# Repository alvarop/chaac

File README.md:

# Chaac - Weather station!

This is a work in progress for a wireless weather station project.

The project consists of:

* [Hardware](hw/) - Main development board design files
* [Firmware](fw/) - Code for the microcontroller
* [Software](sw/) - Python scripts to communicate with the weather station, log, and plot data

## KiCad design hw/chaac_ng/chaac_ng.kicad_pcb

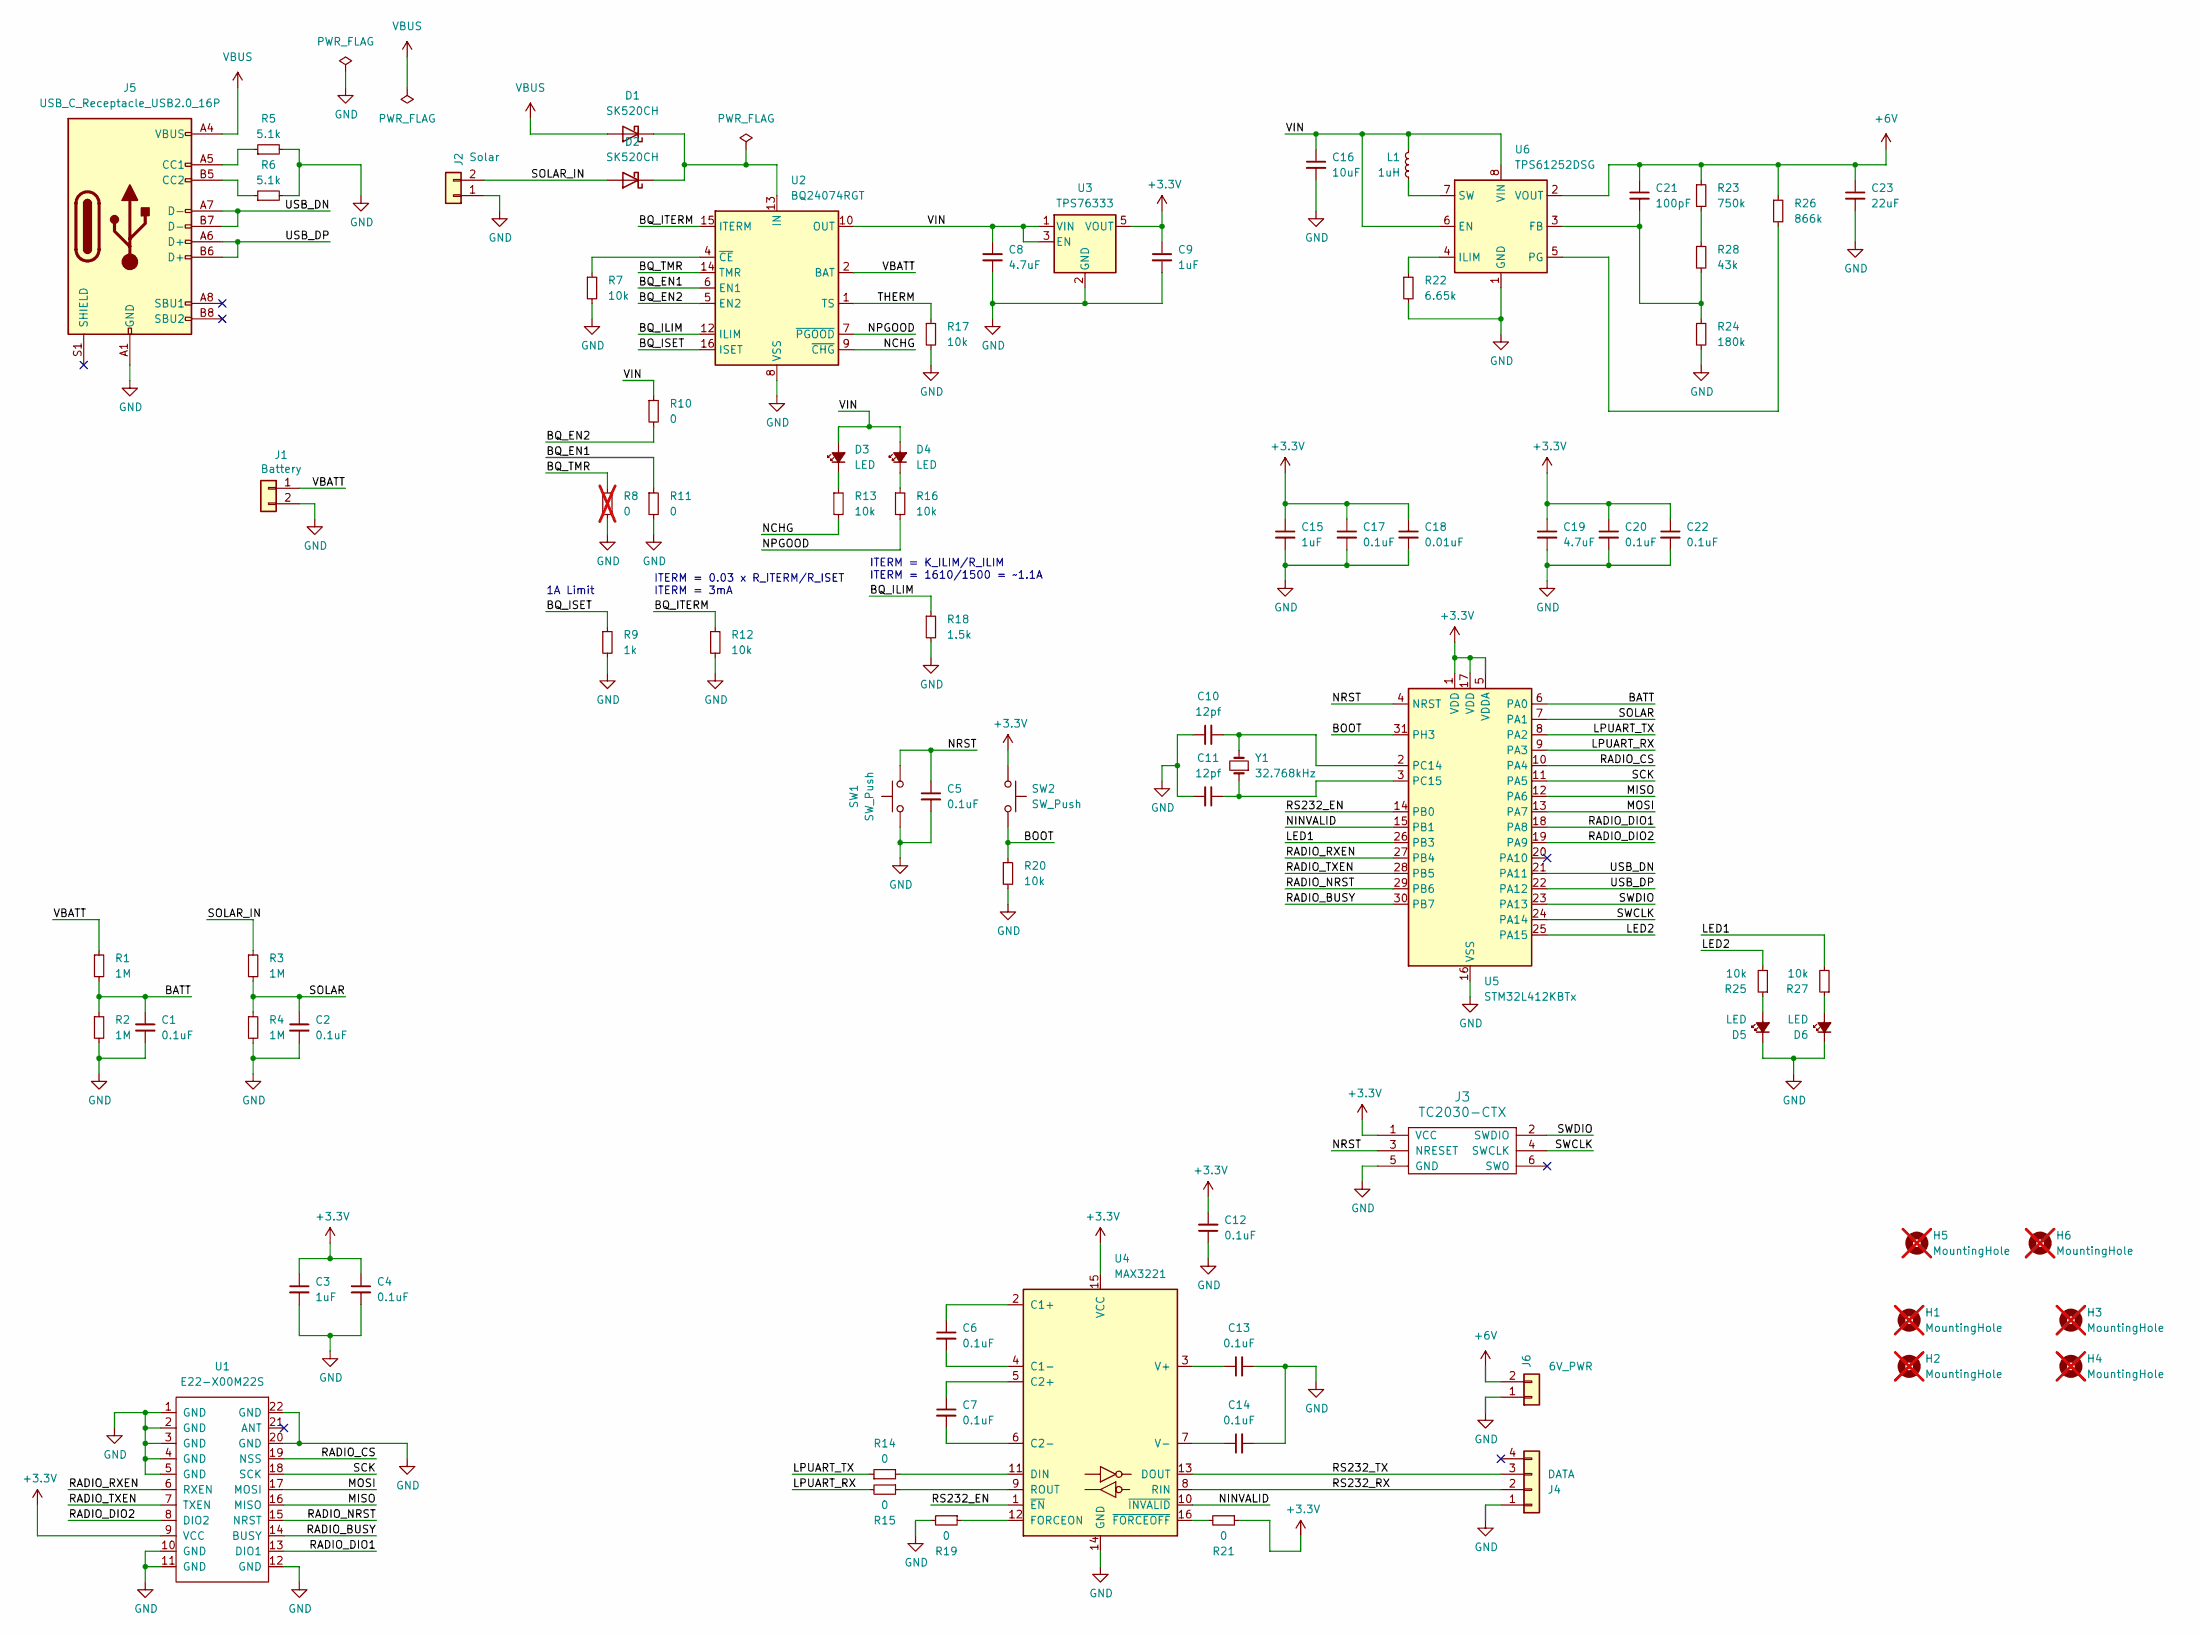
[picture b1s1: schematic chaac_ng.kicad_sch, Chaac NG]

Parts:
C1, C2, C4, C5, C6, C7, C12, C13, C14, C17, C20, C22: 0.1uF; C_0402_1005Metric; MPN CL05B104KB54PNC; LCSC C307331
C3, C9, C15: 1uF; C_0402_1005Metric; MPN CL05A105KA5NQNC; LCSC C52923
C8, C19: 4.7uF; C_0402_1005Metric; MPN CL05A475MP5NRNC; LCSC C23733
C10, C11: 12pf; C_0402_1005Metric; MPN 0402CG120J500NT; LCSC C1547
C16: 10uF; C_0603_1608Metric; MPN CL10A106MA8NRNC; LCSC C96446
C18: 0.01uF; C_0402_1005Metric; MPN CL05B103KB5NNNC; LCSC C15195
C21: 100pF; C_0402_1005Metric; MPN 0402CG101J500NT; LCSC C1546
C23: 22uF; C_1210_3225Metric; MPN TMK325B7226KMHP; LCSC C386098
D1, D2: SK520CH; SK520_DO-214AB; MPN SK520CHV6G; LCSC C483994
D3, D4, D5, D6: LED; LED_0603_1608Metric; MPN KT-0603R; LCSC C2286
H1, H2, H3, H4: MountingHole; MountingHole_3.2mm_M3; not fitted
H5, H6: MountingHole; ZIPTIE_HOLE_4x2mm; not fitted
J1: Battery; S2B-PH-SM4-TB; MPN S2B-PH-SM4-TB(LF)(SN); LCSC C295747
J2: Solar; TerminalBlock_TE_282834-2_1x02_P2.54mm_Horizontal; MPN 282834-2; LCSC C918120
J3: TC2030-CTX; TC2030-NL
J4: DATA; TerminalBlock_TE_282834-4_1x04_P2.54mm_Horizontal; MPN 282834-4; LCSC C918122
J5: USB_C_Receptacle_USB2.0_16P; USB-C-SMD_TYPE-C16PIN; MPN TYPE-C16PIN; LCSC C393939
J6: 6V_PWR; TerminalBlock_TE_282834-2_1x02_P2.54mm_Horizontal; MPN 282834-2; LCSC C918120
L1: 1uH; L_0806; MPN DFE201610E-1R0M=P2; LCSC C161082
R1, R2, R3, R4: 1M; R_0402_1005Metric; LCSC C26083
R5, R6: 5.1k; R_0402_1005Metric; LCSC C25905
R7, R12, R13, R16, R17, R20, R25, R27: 10k; R_0402_1005Metric; LCSC C25744
R8: 0; R_0402_1005Metric; LCSC C17168; not fitted
R9: 1k; R_0402_1005Metric; LCSC C11702
R10, R11, R14, R15, R19, R21: 0; R_0402_1005Metric; LCSC C17168
R18: 1.5k; R_0402_1005Metric; LCSC C25867
R22: 6.65k; R_0402_1005Metric; LCSC C227201
R23: 750k; R_0402_1005Metric; LCSC C137937
R24: 180k; R_0402_1005Metric; LCSC C138046
R26: 866k; R_0402_1005Metric; LCSC C227250
R28: 43k; R_0402_1005Metric; LCSC C227081
SW1, SW2: SW_Push; SW-SMD_L3.9-W3.0-P4.45; MPN SKRKAEE020; LCSC C115357
U1: E22-X00M22S; MPN E22-900M22S; LCSC C411293
U2: BQ24074RGT; VQFN-16-1EP_3x3mm_P0.5mm_EP1.6x1.6mm; MPN BQ24074RGTR; LCSC C54313
U3: TPS76333; SOT-23-5; MPN TCR3DF33,LM(CT; LCSC C146356
U4: MAX3221; TSSOP-16_4.4x5mm_P0.65mm; MPN MAX3221EIPWR; LCSC C484736
U5: STM32L412KBTx; LQFP-32_7x7mm_P0.8mm; MPN STM32L412KBT6; LCSC C529438
U6: TPS61252DSG; WSON-8-1EP_2x2mm_P0.5mm_EP0.9x1.6mm; MPN TPS61252DSGR; LCSC C128617
Y1: 32.768kHz; ABS05; MPN ABS05-32.768KHZ-9-T; LCSC C596929

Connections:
+3.3V: C3.1, C4.1, C9.1, C12.2, C15.1, C17.1, C18.1, C19.1, C20.1, C22.1, J3.1 (VCC), R21.1, SW2.1, U1.9 (VCC), U3.5 (VOUT), U4.15 (VCC), U5.1 (VDD), U5.5 (VDDA), U5.17 (VDD)
+6V: C21.1, C23.1, J6.2, R23.1, R26.1, U6.2 (VOUT)
/BATT: C1.1, R1.2, R2.1, U5.6 (PA0)
/BOOT: R20.1, SW2.2, U5.31 (PH3)
/BQ_EN1: R11.1, U2.6 (EN1)
/BQ_EN2: R10.2, U2.5 (EN2)
/BQ_ILIM: R18.1, U2.12 (ILIM)
/BQ_ISET: R9.1, U2.16 (ISET)
/BQ_ITERM: R12.1, U2.15 (ITERM)
/BQ_TMR: R8.1, U2.14 (TMR)
/LED1: R27.2, U5.26 (PB3)
/LED2: R25.2, U5.25 (PA15)
/LPUART_RX: R15.2, U5.9 (PA3)
/LPUART_TX: R14.1, U5.8 (PA2)
/MISO: U1.16 (MISO), U5.12 (PA6)
/MOSI: U1.17 (MOSI), U5.13 (PA7)
/NCHG: R13.2, U2.9 (~CHG)
/NINVALID: U4.10 (~INVALID), U5.15 (PB1)
/NPGOOD: R16.2, U2.7 (~PGOOD)
/NRST: C5.1, J3.3 (NRESET), SW1.2, U5.4 (NRST)
/RADIO_BUSY: U1.14 (BUSY), U5.30 (PB7)
/RADIO_CS: U1.19 (NSS), U5.10 (PA4)
/RADIO_DIO1: U1.13 (DIO1), U5.18 (PA8)
/RADIO_DIO2: U1.8 (DIO2), U5.19 (PA9)
/RADIO_NRST: U1.15 (NRST), U5.29 (PB6)
/RADIO_RXEN: U1.6 (RXEN), U5.27 (PB4)
/RADIO_TXEN: U1.7 (TXEN), U5.28 (PB5)
/RS232_EN: U4.1 (~EN), U5.14 (PB0)
/RS232_RX: J4.2, U4.8 (RIN)
/RS232_TX: J4.3, U4.13 (DOUT)
/SCK: U1.18 (SCK), U5.11 (PA5)
/SOLAR: C2.1, R3.2, R4.1, U5.7 (PA1)
/SOLAR_IN: D2.2 (A), J2.2, R3.1
/SWCLK: J3.4 (SWCLK), U5.24 (PA14)
/SWDIO: J3.2 (SWDIO), U5.23 (PA13)
/THERM: R17.1, U2.1 (TS)
/USB_DN: J5.A7 (D-), J5.B7 (D-), U5.21 (PA11)
/USB_DP: J5.A6 (D+), J5.B6 (D+), U5.22 (PA12)
/VBATT: J1.1, R1.1, U2.2 (BAT), U2.3 (BAT)
/VIN: C8.1, C16.1, D3.2 (A), D4.2 (A), L1.1, R10.1, U2.10 (OUT), U2.11 (OUT), U3.1 (VIN), U3.3 (EN), U6.6 (EN), U6.8 (VIN)
GND: C1.2, C2.2, C3.2, C4.2, C5.2, C8.2, C9.2, C10.1, C11.2, C12.1, C13.2, C14.2, C15.2, C16.2, C17.2, C18.2, C19.2, C20.2, C22.2, C23.2, D5.1 (K), D6.1 (K), J1.2, J2.1, J3.5 (GND), J4.1, J5.A1 (GND), J5.A12 (GND), J5.B1 (GND), J5.B12 (GND), J6.1, R2.2, R4.2, R5.2, R6.2, R7.2, R8.2, R9.2, R11.2, R12.2, R17.2, R18.2, R19.2, R20.2, R22.2, R24.2, SW1.1, U1.1 (GND), U1.2 (GND), U1.3 (GND), U1.4 (GND), U1.5 (GND), U1.10 (GND), U1.11 (GND), U1.12 (GND), U1.20 (GND), U1.22 (GND), U2.8 (VSS), U2.17 (VSS), U3.2 (GND), U4.14 (GND), U5.16 (VSS), U5.32 (VSS), U6.1 (GND), U6.9 (GND)
unnamed: D1.1 (K), D2.1 (K), U2.13 (IN)
unnamed: D3.1 (K), R13.1
unnamed: D4.1 (K), R16.1
unnamed: D5.2 (A), R25.1
unnamed: D6.2 (A), R27.1
unnamed: J5.A5 (CC1), R5.1
unnamed: J5.B5 (CC2), R6.1
unnamed: R23.2, R28.1
unnamed: R7.1, U2.4 (~CE)
unnamed: C6.1, U4.2 (C1+)
unnamed: C6.2, U4.4 (C1-)
unnamed: C7.1, U4.5 (C2+)
unnamed: C7.2, U4.6 (C2-)
unnamed: R14.2, U4.11 (DIN)
unnamed: R19.1, U4.12 (FORCEON)
unnamed: R15.1, U4.9 (ROUT)
unnamed: C13.1, U4.3 (V+)
unnamed: C14.1, U4.7 (V-)
unnamed: R21.2, U4.16 (~FORCEOFF)
unnamed: C10.2, U5.2 (PC14), Y1.2
unnamed: C11.1, U5.3 (PC15), Y1.1
unnamed: C21.2, R24.1, R28.2, U6.3 (FB)
unnamed: R22.1, U6.4 (ILIM)
unnamed: R26.2, U6.5 (PG)
unnamed: L1.2, U6.7 (SW)
VBUS: D1.2 (A), J5.A4 (VBUS), J5.A9 (VBUS), J5.B4 (VBUS), J5.B9 (VBUS)

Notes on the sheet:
ITERM = K_ILIM/R_ILIM ITERM = 1610/1500 = ~1.1A
ITERM = 0.03 x R_ITERM/R_ISET ITERM = 3mA
1A Limit

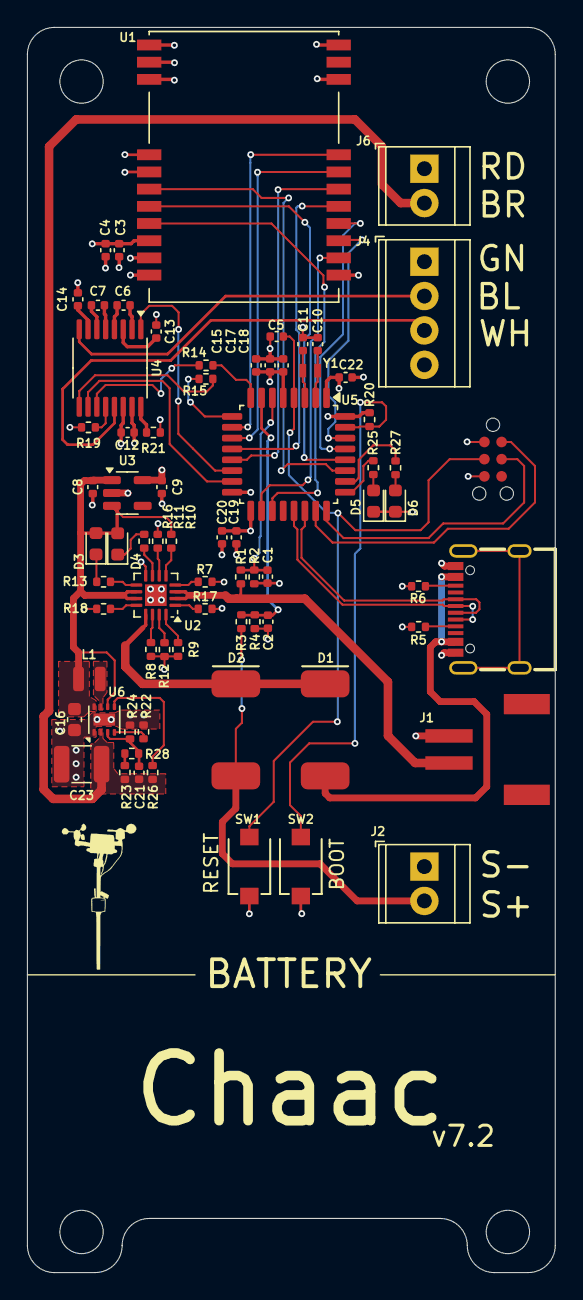
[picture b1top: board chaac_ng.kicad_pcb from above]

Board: 4 copper layers, 39.0 x 92.0 mm, 79 parts (0 on the bottom side), 67 nets.

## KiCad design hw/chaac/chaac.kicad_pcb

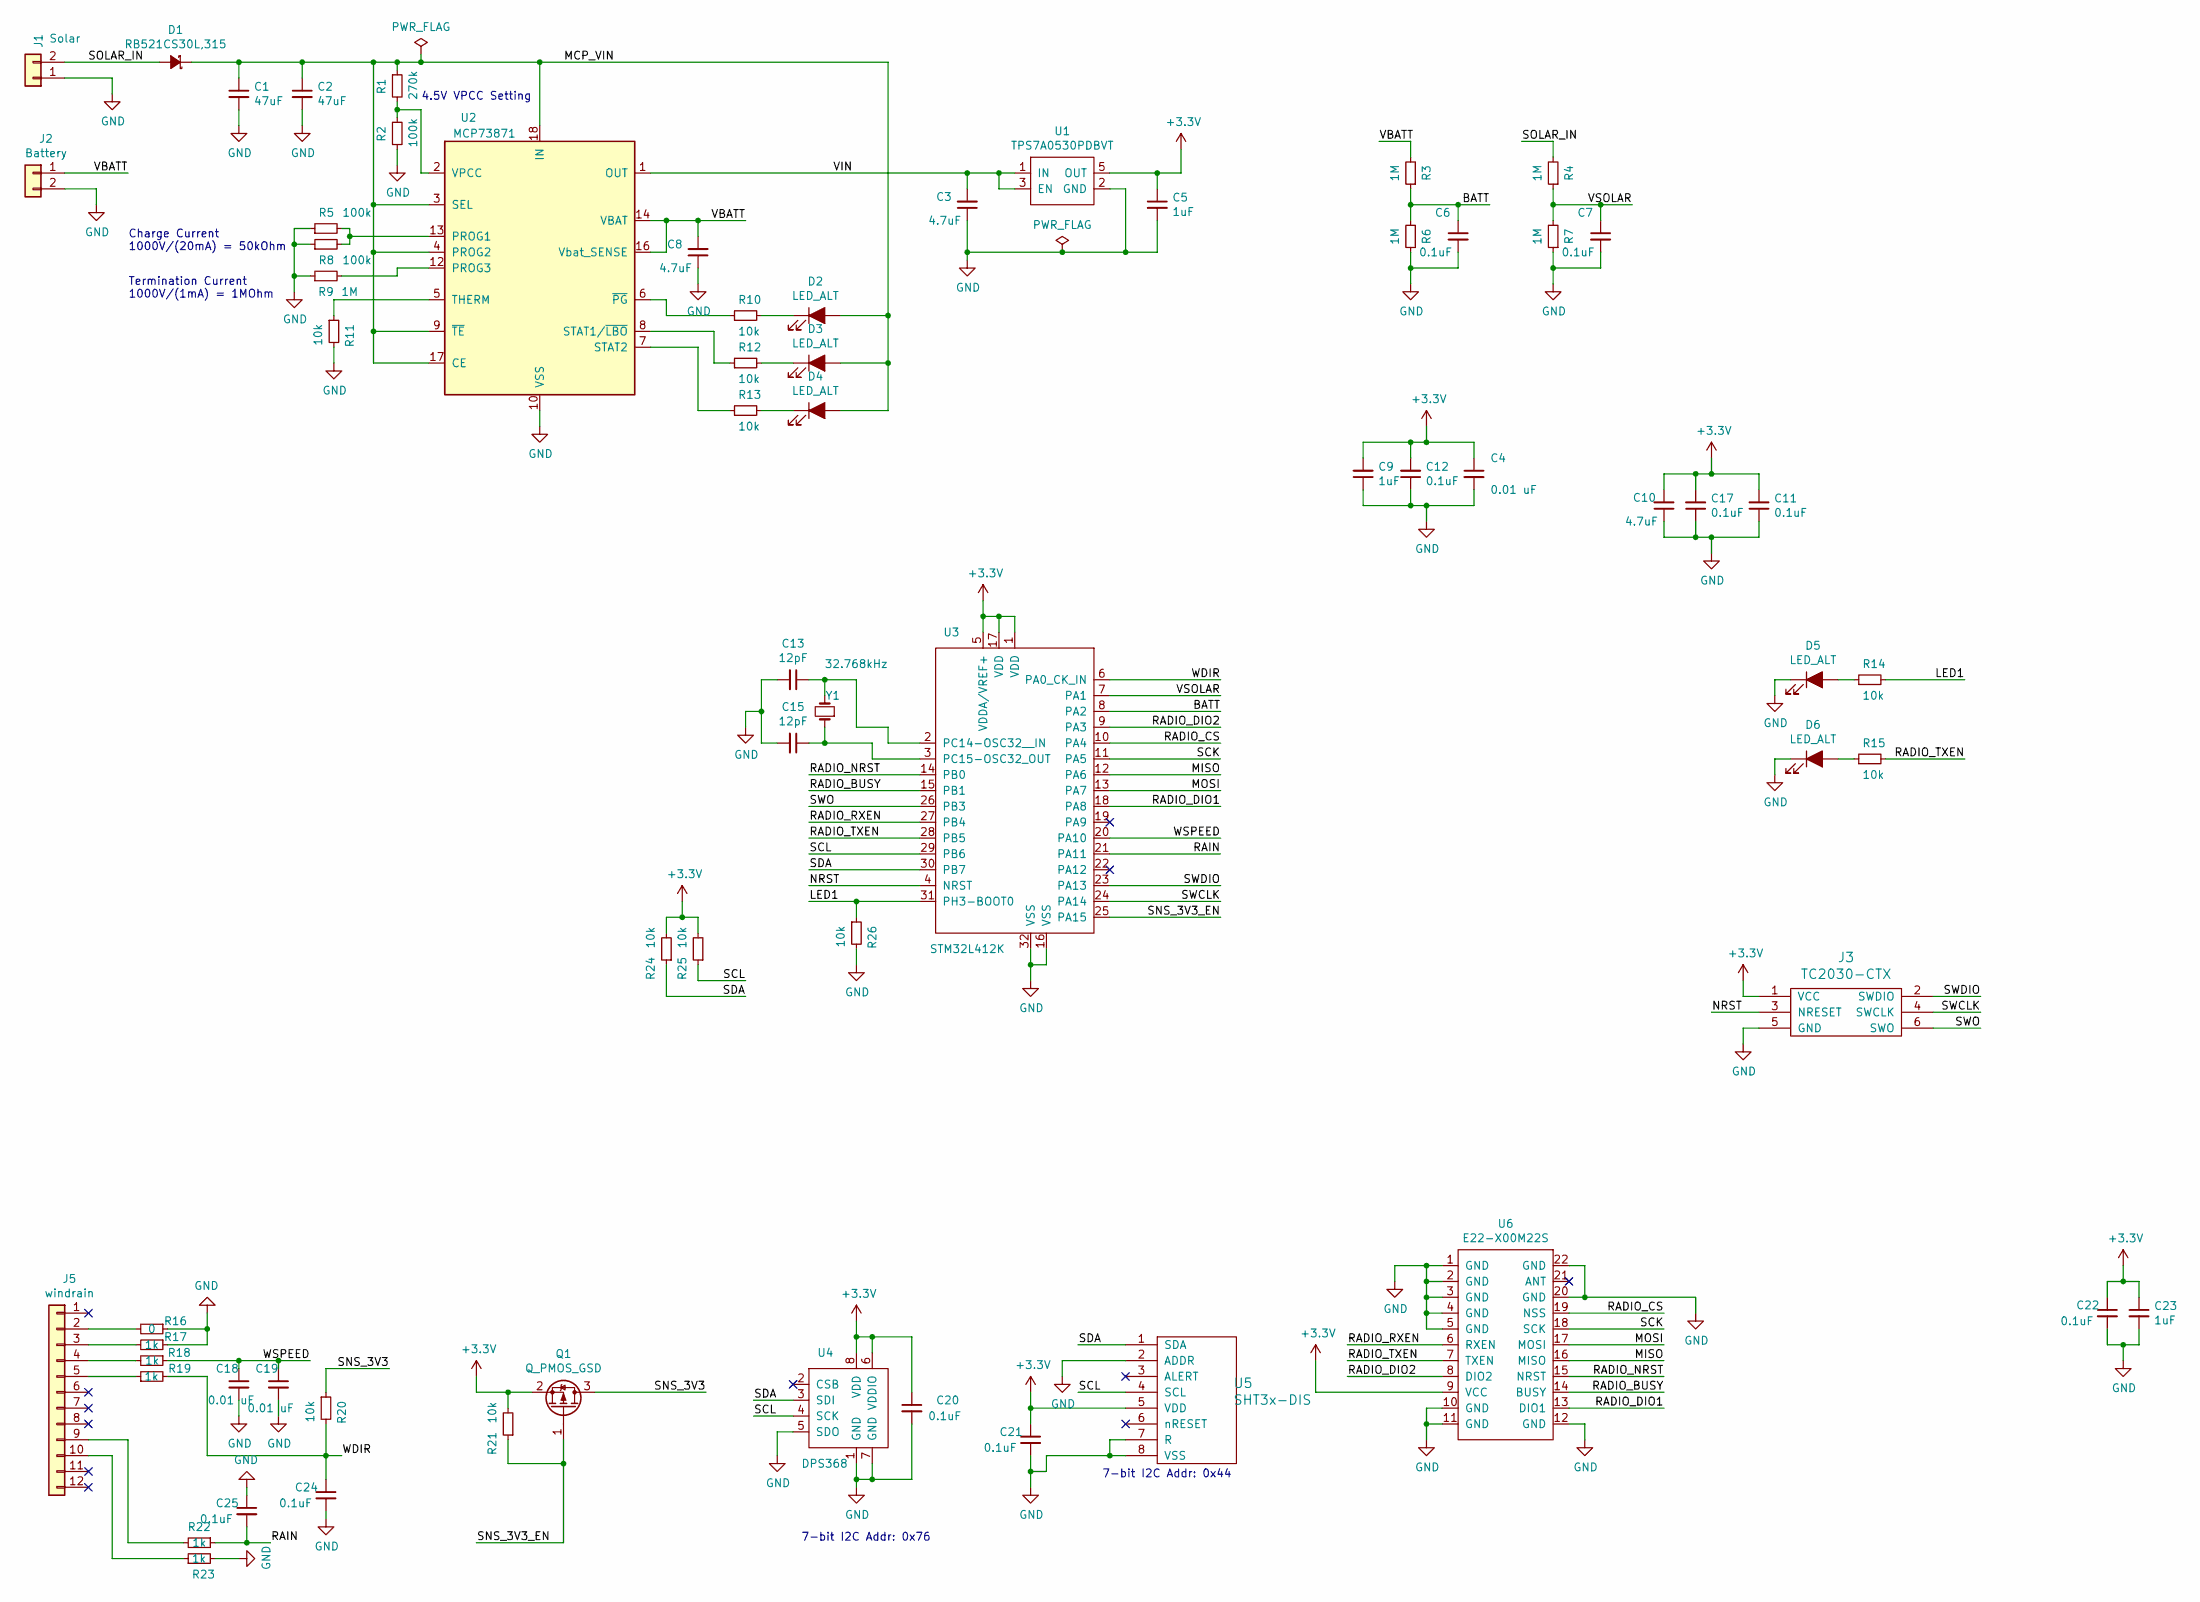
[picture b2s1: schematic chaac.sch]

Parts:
C1, C2: 47uF; C_1206_3216Metric; MPN CL31A476MPHNNNE
C3, C8, C10: 4.7uF; C_0402_1005Metric; MPN CL05A475MP5NRNC
C4, C18, C19: 0.01 uF; C_0402_1005Metric; MPN CL05B103KB5NNNC
C5, C9, C23: 1uF; C_0402_1005Metric; MPN C1005X5R1V105K050BE
C6, C7, C11, C12, C17, C20, C21, C22, C24, C25: 0.1uF; C_0402_1005Metric; MPN GRM155R61A104KA01D
C13, C15: 12pF; C_0402_1005Metric; MPN C0402C120J5GACTU
D1: RB521CS30L,315; RB521CS30L; MPN RB521CS30L,315
D2, D3, D4, D5, D6: LED_ALT; LED_0603_1608Metric; MPN SML-D12U1WT86
J1: Solar; TerminalBlock_TE_282834-2_1x02_P2.54mm_Horizontal; MPN 282834-2
J2: Battery; S2B-PH-SM4-TB; MPN S2B-PH-SM4-TB(LF)(SN)
J3: TC2030-CTX; TC2030-NL
J5: windrain; 043814-6621; MPN 0438146621
Q1: Q_PMOS_GSD; SOT-23; MPN FDV304P
R1: 270k; R_0402_1005Metric; MPN RC0402FR-07270KL
R2, R5, R8: 100k; R_0402_1005Metric; MPN RC0402FR-07100KL
R3, R4, R6, R7, R9: 1M; R_0402_1005Metric; MPN CRCW04021M00FKEDC
R10, R11, R12, R13, R14, R15, R20, R21, R24, R25, R26: 10k; R_0402_1005Metric; MPN RC0402JR-0710KL
R16: 0; R_0402_1005Metric
R17, R18, R19, R22, R23: 1k; R_0402_1005Metric; MPN CRG0402J1K0
U1: TPS7A0530PDBVT; SOT-23(M5); MPN TPS7A0530PDBVT
U2: MCP73871; MPN MCP73871T-2CCI/ML
U3: STM32L412K; UFQFPN32-ALT; MPN STM32L412KBU6
U4: DPS368; MPN DPS368XTSA1
U5: SHT3x-DIS; SHT3x; MPN SHT31-DIS-F2.5KS
U6: E22-X00M22S
Y1: 32.768kHz; ABS05; MPN ABS05-32.768KHZ-9-T

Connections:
+3V3: C4.1, C5.1, C9.2, C10.2, C11.2, C12.2, C17.2, C20.1, C21.1, C22.1, C23.1, J3.1 (VCC), Q1.2 (S), R21.2, R24.2, R25.2, U1.5 (OUT), U3.1 (VDD), U3.5 (VDDA/VREF+), U3.17 (VDD), U4.6 (VDDIO), U4.8 (VDD), U5.5 (VDD), U6.9 (VCC)
/BATT: C6.1, R3.1, R6.2, U3.8 (PA2)
/LED1: R14.2, R26.1, U3.31 (PH3-BOOT0)
/MCP_VIN: C1.1, C2.1, D1.1 (K), D2.2 (A), D3.2 (A), D4.2 (A), R1.1, U2.3 (SEL), U2.4 (PROG2), U2.9 (~TE), U2.17 (CE), U2.18 (IN), U2.19 (IN)
/MISO: U3.12 (PA6), U6.16 (MISO)
/MOSI: U3.13 (PA7), U6.17 (MOSI)
/NRST: J3.3 (NRESET), U3.4 (NRST)
/RADIO_BUSY: U3.15 (PB1), U6.14 (BUSY)
/RADIO_CS: U3.10 (PA4), U6.19 (NSS)
/RADIO_DIO1: U3.18 (PA8), U6.13 (DIO1)
/RADIO_DIO2: U3.9 (PA3), U6.8 (DIO2)
/RADIO_NRST: U3.14 (PB0), U6.15 (NRST)
/RADIO_RXEN: U3.27 (PB4), U6.6 (RXEN)
/RADIO_TXEN: R15.2, U3.28 (PB5), U6.7 (TXEN)
/RAIN: C25.2, R22.1, U3.21 (PA11)
/SCK: U3.11 (PA5), U6.18 (SCK)
/SCL: R25.1, U3.29 (PB6), U4.4 (SCK), U5.4 (SCL)
/SDA: R24.1, U3.30 (PB7), U4.3 (SDI), U5.1 (SDA)
/SNS_3V3: Q1.3 (D), R20.1
/SNS_3V3_EN: Q1.1 (G), R21.1, U3.25 (PA15)
/SOLAR_IN: D1.2 (A), J1.2, R4.2
/SWCLK: J3.4 (SWCLK), U3.24 (PA14)
/SWDIO: J3.2 (SWDIO), U3.23 (PA13)
/SWO: J3.6 (SWO), U3.26 (PB3)
/VBATT: C8.2, J2.1, R3.2, U2.14 (VBAT), U2.15 (VBAT), U2.16 (Vbat_SENSE)
/VIN: C3.2, U1.1 (IN), U1.3 (EN), U2.1 (OUT), U2.20 (OUT)
/VSOLAR: C7.1, R4.1, R7.2, U3.7 (PA1)
/WDIR: C24.1, R19.2, R20.2, U3.6 (PA0_CK_IN)
/WSPEED: C18.1, C19.1, R18.1, U3.20 (PA10)
GND: C1.2, C2.2, C3.1, C4.2, C5.2, C6.2, C7.2, C8.1, C9.1, C10.1, C11.1, C12.1, C13.2, C15.2, C17.1, C18.2, C19.2, C20.2, C21.2, C22.2, C23.2, C24.2, C25.1, D5.1 (K), D6.1 (K), J1.1, J2.2, J3.5 (GND), R2.2, R5.1, R6.1, R7.1, R8.1, R9.1, R11.2, R16.1, R17.1, R23.2, R26.2, U1.2 (GND), U2.10 (VSS), U2.11 (VSS), U2.21 (VSS), U3.16 (VSS), U3.32 (VSS), U4.1 (GND), U4.5 (SDO), U4.7 (GND), U5.2 (ADDR), U5.7 (R), U5.8 (VSS), U6.1 (GND), U6.2 (GND), U6.3 (GND), U6.4 (GND), U6.5 (GND), U6.10 (GND), U6.11 (GND), U6.12 (GND), U6.20 (GND), U6.22 (GND)
unnamed: C13.1, U3.2 (PC14-OSC32__IN), Y1.2
unnamed: C15.1, U3.3 (PC15-OSC32_OUT), Y1.1
unnamed: D2.1 (K), R10.2
unnamed: D3.1 (K), R12.2
unnamed: D4.1 (K), R13.2
unnamed: D5.2 (A), R14.1
unnamed: D6.2 (A), R15.1
unnamed: J5.2, R16.2
unnamed: J5.3, R17.2
unnamed: J5.4, R18.2
unnamed: J5.5, R19.1
unnamed: J5.9, R22.2
unnamed: J5.10, R23.1
unnamed: R1.2, R2.1, U2.2 (VPCC)
unnamed: R5.2, R8.2, U2.13 (PROG1)
unnamed: R9.2, U2.12 (PROG3)
unnamed: R10.1, U2.6 (~PG~)
unnamed: R11.1, U2.5 (THERM)
unnamed: R12.1, U2.8 (STAT1/~LBO~)
unnamed: R13.1, U2.7 (STAT2)

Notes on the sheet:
7-bit I2C Addr: 0x76
7-bit I2C Addr: 0x44
Charge Current 1000V/(20mA) = 50kOhm
Termination Current 1000V/(1mA) = 1MOhm
4.5V VPCC Setting

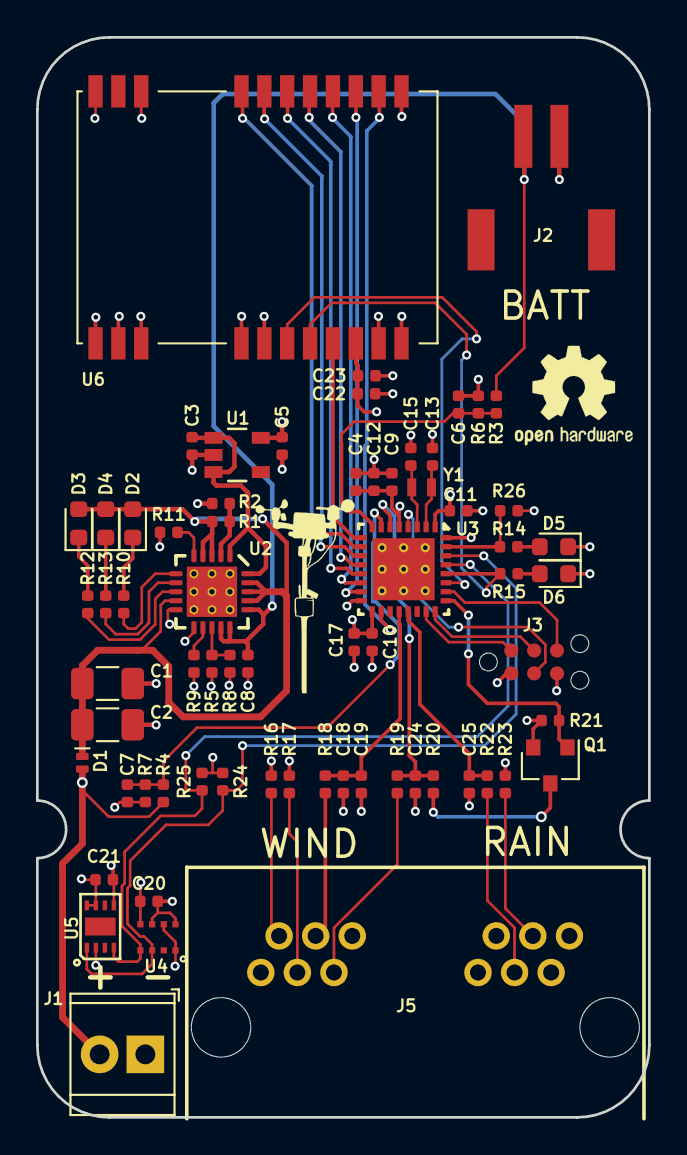
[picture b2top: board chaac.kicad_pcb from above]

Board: 4 copper layers, 34.0 x 60.0 mm, 67 parts (0 on the bottom side), 50 nets.

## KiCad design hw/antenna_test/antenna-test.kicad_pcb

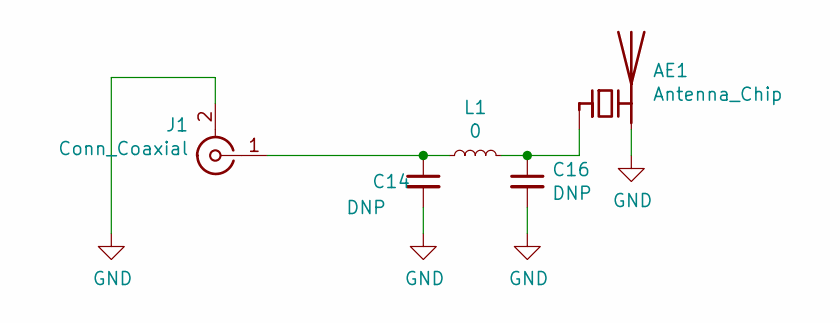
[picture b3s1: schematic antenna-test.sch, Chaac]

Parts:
AE1: Antenna_Chip; W3211
C14, C16: DNP; C_0402_1005Metric
J1: Conn_Coaxial; TE-2337019-1
L1: 0; L_0402_1005Metric

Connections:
GND: AE1.2 (PCB_Trace), C14.2, C16.2, J1.2 (Ext)
unnamed: AE1.1 (FEED), C16.1, L1.2
unnamed: C14.1, J1.1 (In), L1.1

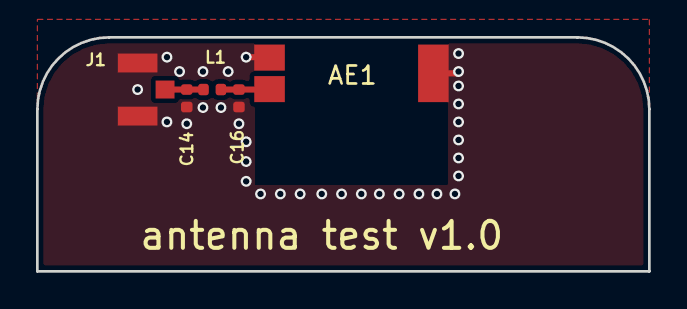
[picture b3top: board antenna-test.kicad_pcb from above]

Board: 4 copper layers, 34.0 x 13.0 mm, 5 parts (0 on the bottom side), 3 nets.

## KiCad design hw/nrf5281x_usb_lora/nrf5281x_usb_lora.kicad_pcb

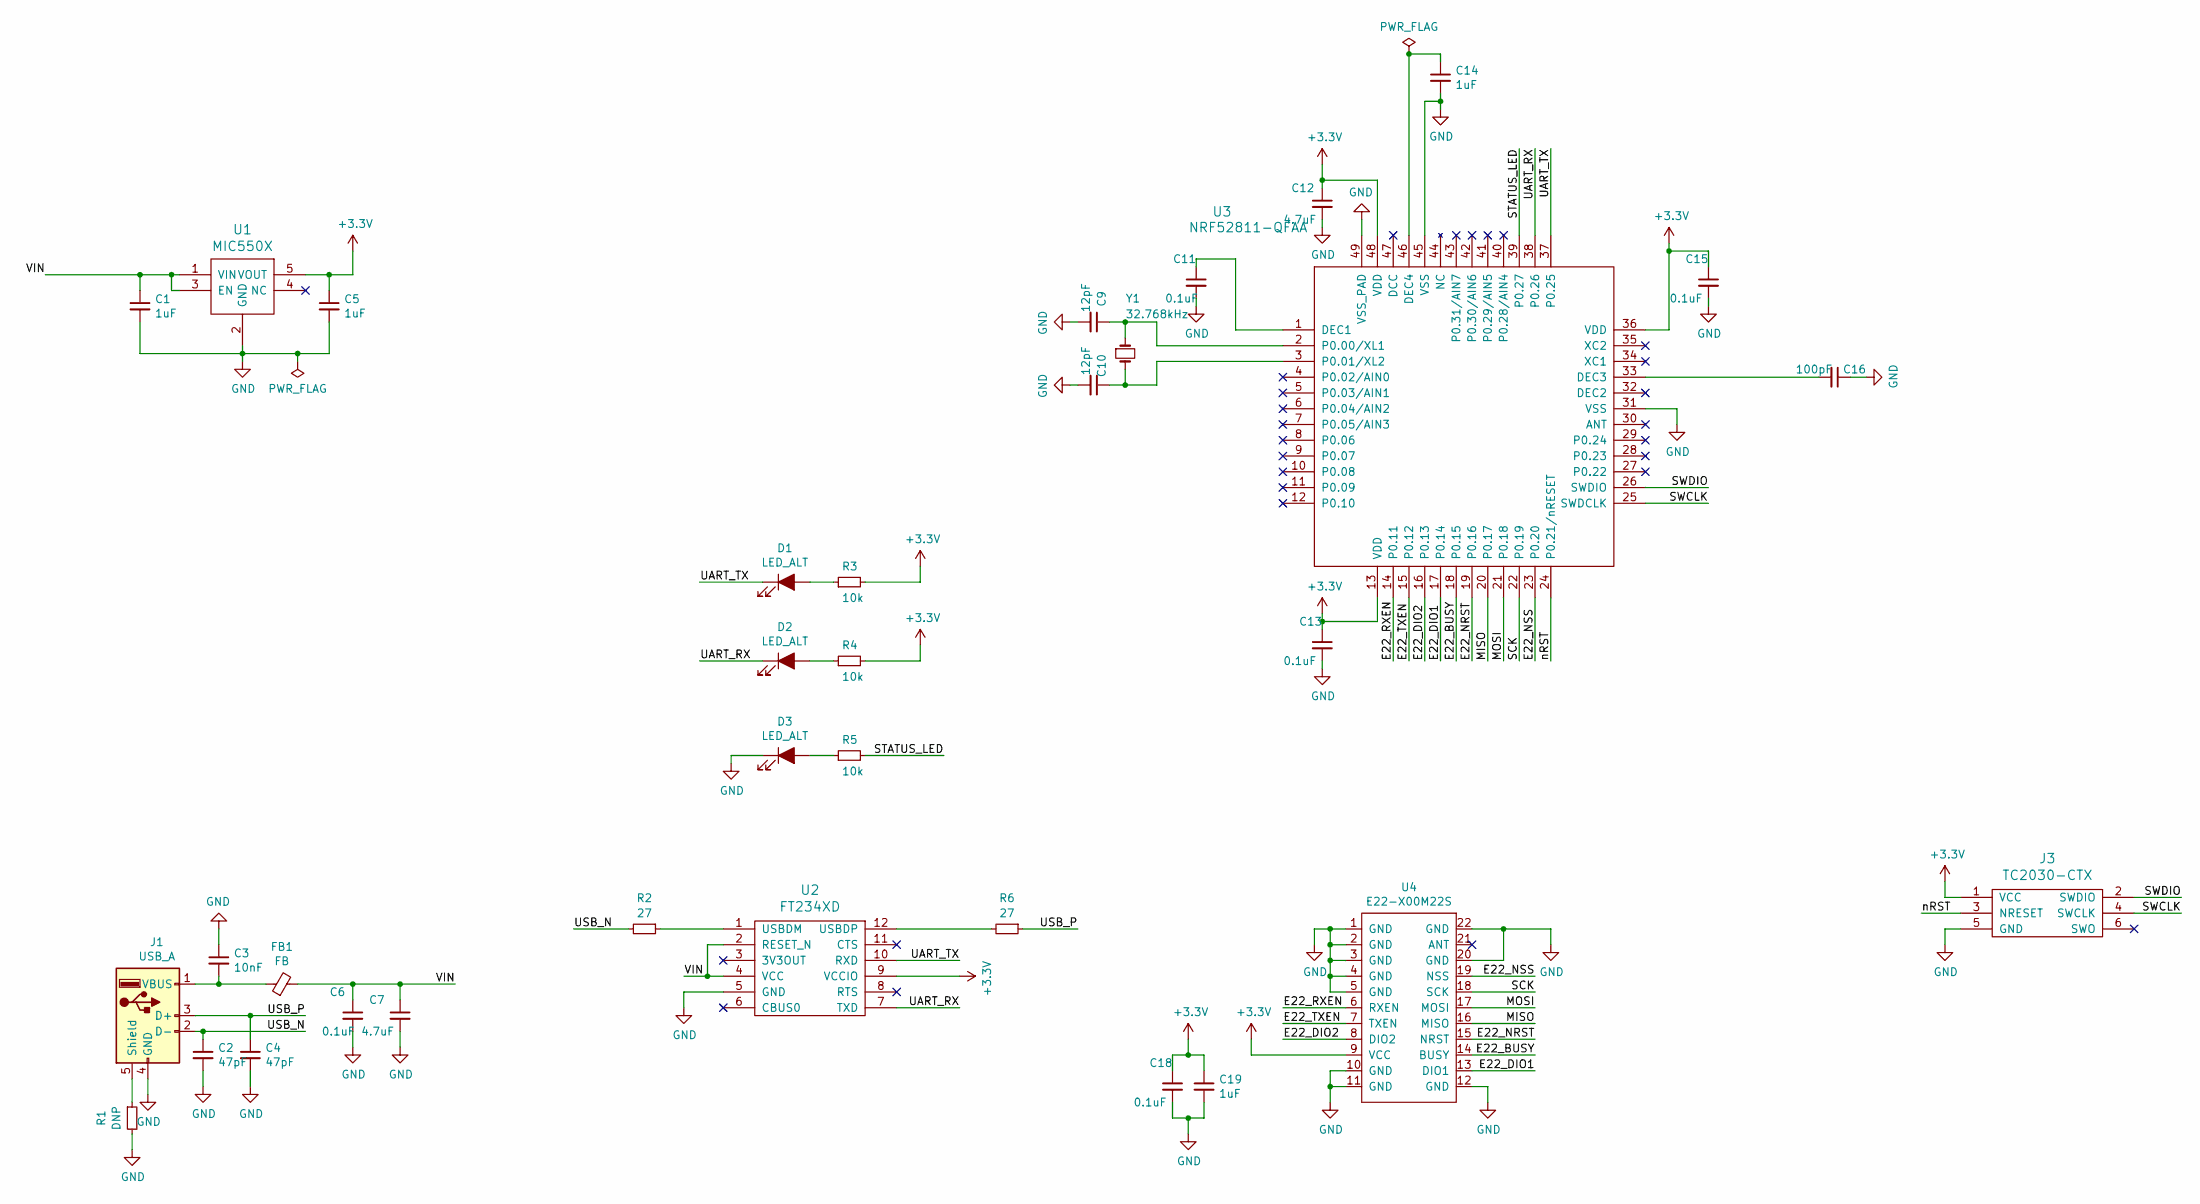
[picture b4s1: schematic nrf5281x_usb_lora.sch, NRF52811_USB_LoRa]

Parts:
C1, C5, C14, C19: 1uF; C_0402_1005Metric; MPN CC0402KRX5R5BB105
C2, C4: 47pF; C_0402_1005Metric; MPN C0402C470K5GACTU
C3: 10nF; C_0402_1005Metric; MPN CL05B103KB5NNNC
C6, C11, C13, C15, C18: 0.1uF; C_0402_1005Metric; MPN GRM155R61A104KA01D
C7, C12: 4.7uF; C_0603_1608Metric; MPN CL10B475KQ8NQNC
C9, C10: 12pF; C_0402_1005Metric; MPN C0402C120J5GACTU
C16: 100pF; C_0402_1005Metric; MPN UMK105CG101JV-F
D1, D2, D3: LED_ALT; LED_0402_1005Metric; MPN QBLP595-IG
FB1: FB; L_0402_1005Metric; MPN BLM15AG601SN1D
J1: USB_A; MOLEX-0480371000; MPN 0480371000
J3: TC2030-CTX; TC2030-NL
R1: DNP; R_0402_1005Metric
R2, R6: 27; R_0402_1005Metric; MPN RC0402JR-0727RL
R3, R4, R5: 10k; R_0402_1005Metric; MPN RC0402JR-0710KL
U1: MIC550X; SOT-23(M5); MPN MIC5504-3.3YM5-TR
U2: FT234XD; FTDI_DFN12; MPN FT234XD-R
U3: NRF52811-QFAA; NRF52811-QFN48-VIAS; MPN ‎NRF52811-QFAA-R‎
U4: E22-X00M22S
Y1: 32.768kHz; ABS05; MPN ABS05-32.768KHZ-9-T

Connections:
+3V3: C5.1, C12.1, C13.1, C15.1, C18.1, C19.1, J3.1 (VCC), R3.2, R4.2, U1.5 (VOUT), U2.9 (VCCIO), U3.13 (VDD), U3.36 (VDD), U3.48 (VDD), U4.9 (VCC)
/E22_BUSY: U3.18 (P0.15), U4.14 (BUSY)
/E22_DIO1: U3.17 (P0.14), U4.13 (DIO1)
/E22_DIO2: U3.16 (P0.13), U4.8 (DIO2)
/E22_NRST: U3.19 (P0.16), U4.15 (NRST)
/E22_NSS: U3.23 (P0.20), U4.19 (NSS)
/E22_RXEN: U3.14 (P0.11), U4.6 (RXEN)
/E22_TXEN: U3.15 (P0.12), U4.7 (TXEN)
/MISO: U3.20 (P0.17), U4.16 (MISO)
/MOSI: U3.21 (P0.18), U4.17 (MOSI)
/SCK: U3.22 (P0.19), U4.18 (SCK)
/STATUS_LED: R5.2, U3.39 (P0.27)
/SWCLK: J3.4 (SWCLK), U3.25 (SWDCLK)
/SWDIO: J3.2 (SWDIO), U3.26 (SWDIO)
/UART_RX: D2.1 (K), U2.7 (TXD), U3.38 (P0.26)
/UART_TX: D1.1 (K), U2.10 (RXD), U3.37 (P0.25)
/USB_N: C2.1, J1.2 (D-), R2.2
/USB_P: C4.1, J1.3 (D+), R6.1
/VIN: C1.1, C6.1, C7.1, FB1.2, U1.1 (VIN), U1.3 (EN), U2.2 (RESET_N), U2.4 (VCC)
/nRST: J3.3 (NRESET), U3.24 (P0.21/nRESET)
GND: C1.2, C2.2, C3.1, C4.2, C5.2, C6.2, C7.2, C9.2, C10.2, C11.2, C12.2, C13.2, C14.2, C15.2, C16.1, C18.2, C19.2, D3.1 (K), J1.4 (GND), J3.5 (GND), R1.2, U1.2 (GND), U2.5 (GND), U3.31 (VSS), U3.45 (VSS), U3.49 (VSS_PAD), U4.1 (GND), U4.2 (GND), U4.3 (GND), U4.4 (GND), U4.5 (GND), U4.10 (GND), U4.11 (GND), U4.12 (GND), U4.20 (GND), U4.22 (GND)
unnamed: C3.2, FB1.1, J1.1 (VBUS)
unnamed: C9.1, U3.2 (P0.00/XL1), Y1.1
unnamed: C10.1, U3.3 (P0.01/XL2), Y1.2
unnamed: C11.1, U3.1 (DEC1)
unnamed: C14.1, U3.46 (DEC4)
unnamed: C16.2, U3.33 (DEC3)
unnamed: D1.2 (A), R3.1
unnamed: D2.2 (A), R4.1
unnamed: D3.2 (A), R5.1
unnamed: J1.5 (Shield), R1.1
unnamed: R2.1, U2.1 (USBDM)
unnamed: R6.2, U2.12 (USBDP)

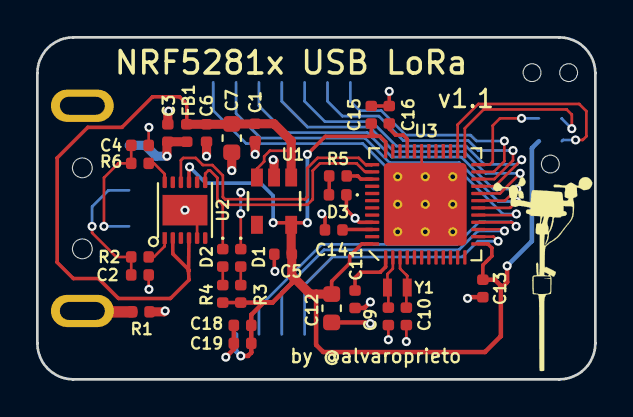
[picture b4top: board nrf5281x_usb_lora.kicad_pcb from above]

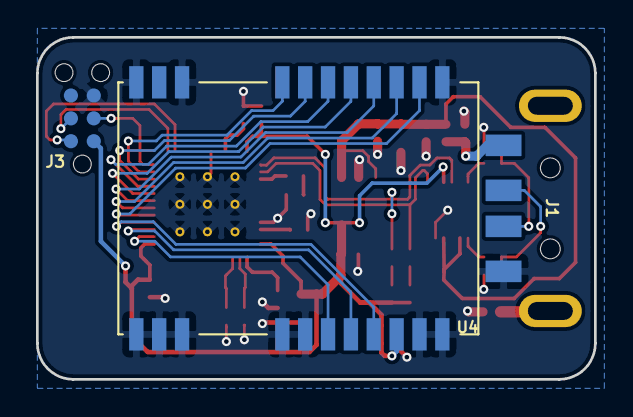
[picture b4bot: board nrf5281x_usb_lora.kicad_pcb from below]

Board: 2 copper layers, 31.0 x 19.0 mm, 34 parts (3 on the bottom side), 33 nets.
